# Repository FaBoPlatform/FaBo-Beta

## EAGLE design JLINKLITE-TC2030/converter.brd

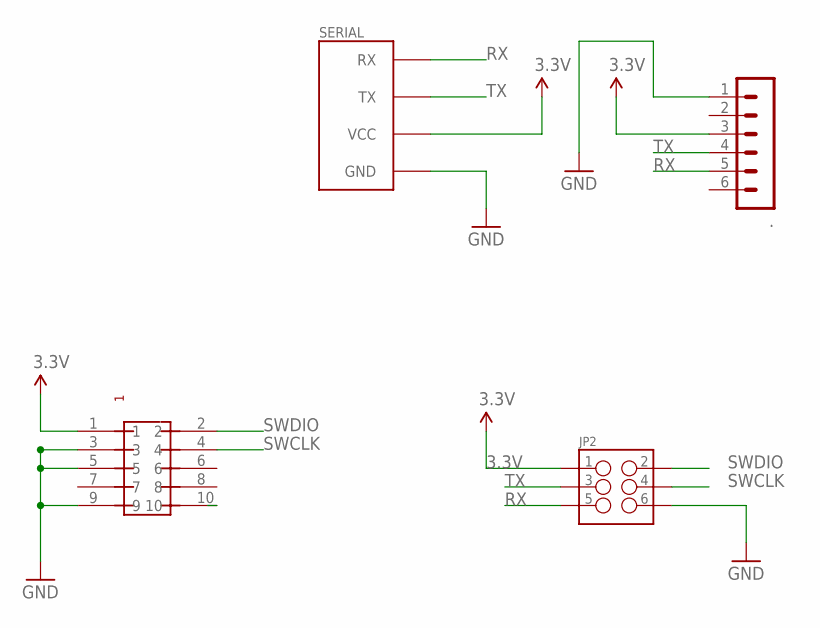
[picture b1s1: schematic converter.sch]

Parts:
.: MA06-1
JP2: M03X2; 2X3-SHROUDED
SERIAL: FABO_BRICK_SERIAL-CONNECTOR_I; FABO_BRICK_SERIAL_CONNECTOR_I
U$5: PIN-HEADER-SMT(1.27MM)2X5

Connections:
3.3V: ..3, JP2.1, SERIAL.VCC, U$5.1
GND: ..1, JP2.6, SERIAL.GND, U$5.3, U$5.5, U$5.9
RESET: U$5.10
RX: ..5, JP2.5, SERIAL.RX
SWCLK: JP2.4, U$5.4
SWDIO: JP2.2, U$5.2
TX: ..4, JP2.3, SERIAL.TX

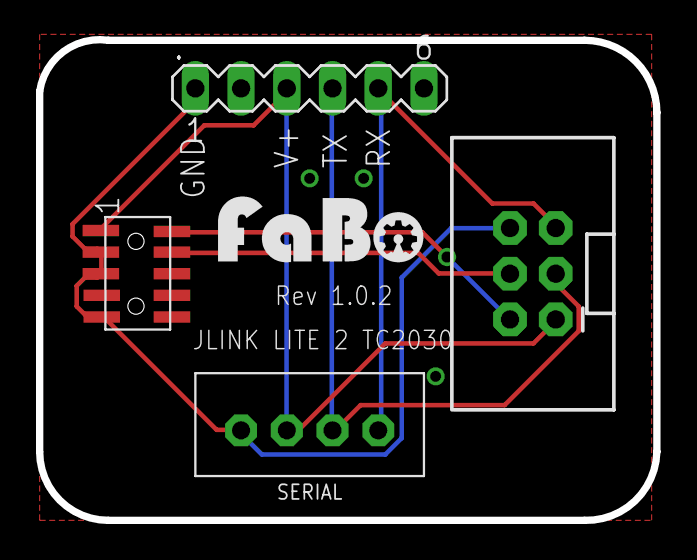
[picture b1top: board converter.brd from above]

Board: 2 copper layers, 34.3 x 26.7 mm, 5 parts (0 on the bottom side), 6 nets.

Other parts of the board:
U$1: LOGO_FABO_M

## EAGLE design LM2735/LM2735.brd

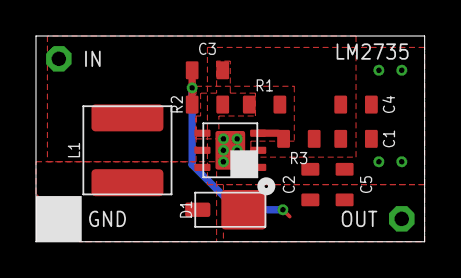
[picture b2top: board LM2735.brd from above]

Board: 2 copper layers, 21.6 x 11.4 mm, 15 parts (0 on the bottom side), 6 nets.

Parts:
C1, C2, C4, C5: 22uF X5R; 0603-NARROW
C3: 1000pF; 0603-NARROW
CN1, CN2, CN3: PIN_1X1_SMALL
D1: ST-MITE
IC1: WSON-6
L1: 22uH; NR5040
R1: 10k 1%; 0603-NARROW
R2: 30.1k 1%; 0603-NARROW
R3: 100k; 0603-NARROW
U$2: LOGO_FABO_MS_BOTTOM

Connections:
FB: C3.1, IC1.4, R1.2, R2.1
GND: C1.1, C2.1, C4.1, C5.1, CN2.1, IC1.1, IC1.5, IC1.7, R1.1
unnamed: IC1.3, R3.2
SW: D1.A, IC1.6, L1.2
VIN: C1.2, C4.2, CN1.1, IC1.2, L1.1, R3.1
VOUT: C2.2, C3.2, C5.2, CN3.1, D1.K, R2.2

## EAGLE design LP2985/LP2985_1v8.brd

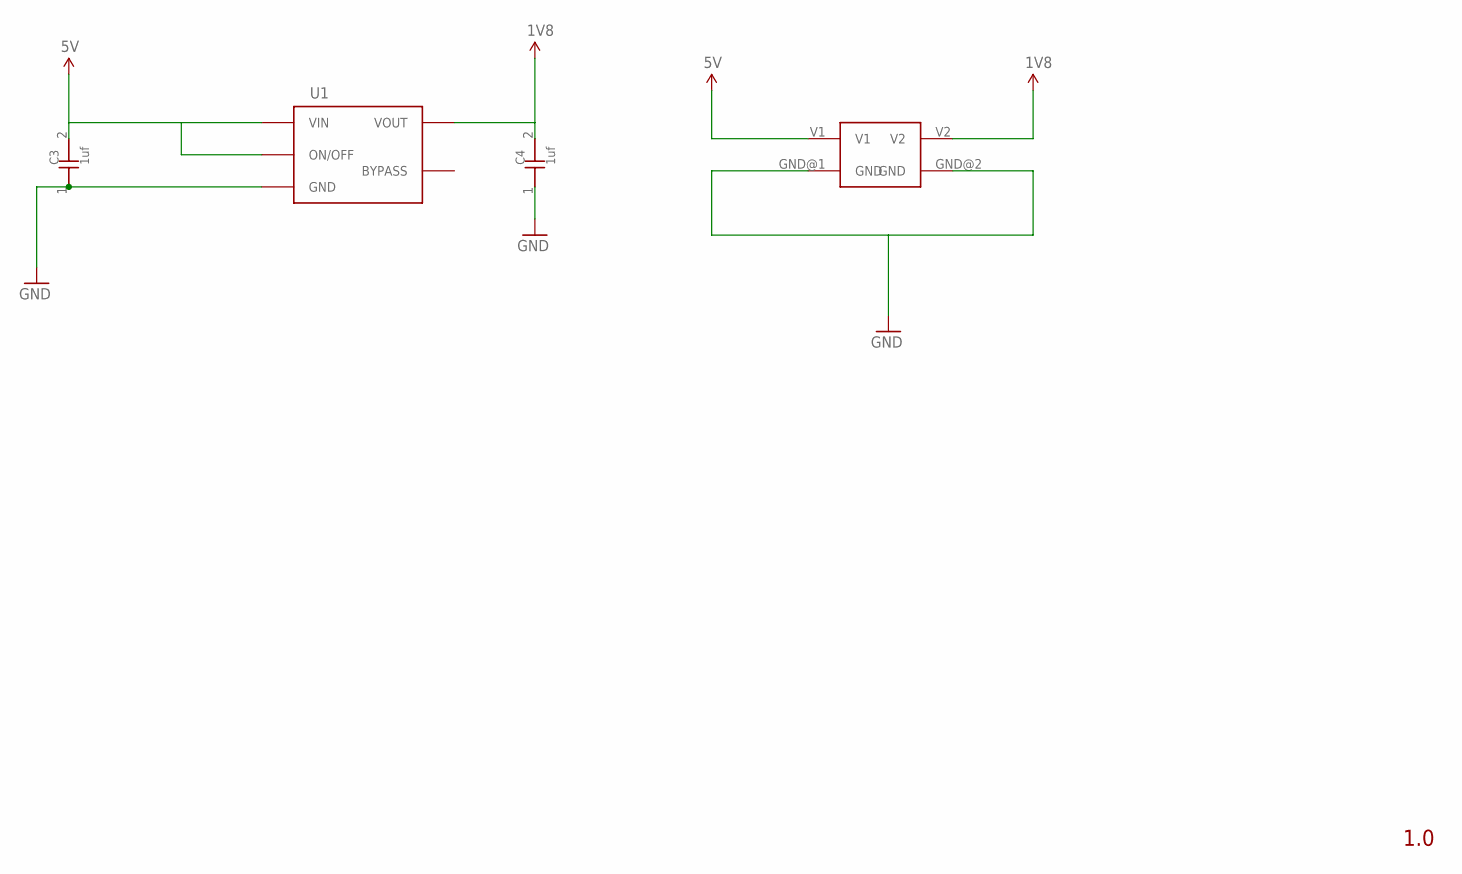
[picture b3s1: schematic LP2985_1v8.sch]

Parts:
C3, C4: 1uf; 0603
U1: LP2985-33DBVR; SOT_23_5
U$2: 4PIN-REGULATOR

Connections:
5V: C3.2, U1.1 (VIN), U1.3 (ON/OFF), U$2.V1
GND: C3.1, C4.1, U1.2 (GND), U$2.GND@1 (GND), U$2.GND@2 (GND)
VCC: C4.2, U1.5 (VOUT), U$2.V2

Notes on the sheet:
1.0

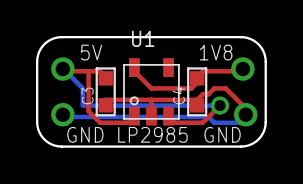
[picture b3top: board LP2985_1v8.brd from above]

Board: 2 copper layers, 12.7 x 6.1 mm, 4 parts (0 on the bottom side), 3 nets.

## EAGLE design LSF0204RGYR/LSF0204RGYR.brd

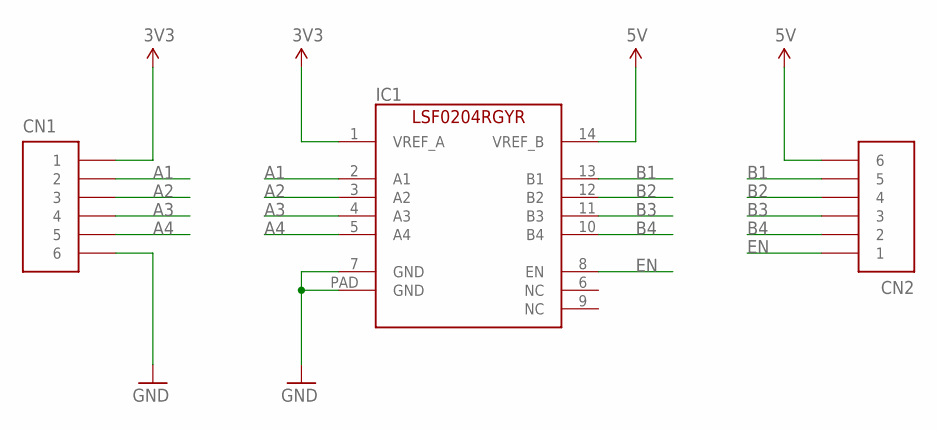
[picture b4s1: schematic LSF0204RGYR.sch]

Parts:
CN1, CN2: PIN_HEADER_1X6-SNEAKY; PIN_1X6_SNEAKY
IC1: LSF0204RGYR; VQFN-14

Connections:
3V3: CN1.1, IC1.1 (VREF_A)
5V: CN2.6, IC1.14 (VREF_B)
A1: CN1.2, IC1.2 (A1)
A2: CN1.3, IC1.3 (A2)
A3: CN1.4, IC1.4 (A3)
A4: CN1.5, IC1.5 (A4)
B1: CN2.5, IC1.13 (B1)
B2: CN2.4, IC1.12 (B2)
B3: CN2.3, IC1.11 (B3)
B4: CN2.2, IC1.10 (B4)
EN: CN2.1, IC1.8 (EN)
GND: CN1.6, IC1.7 (GND), IC1.PAD (GND)

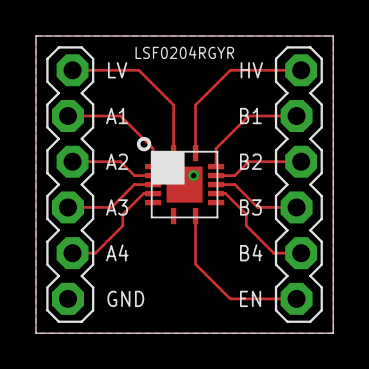
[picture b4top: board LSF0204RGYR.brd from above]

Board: 2 copper layers, 16.5 x 16.5 mm, 3 parts (0 on the bottom side), 12 nets.

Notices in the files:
parts and their libraries:
SparkFun-Connectors: Licensing: CC v3.0 Share-Alike You are welcome to use this library for commercial purposes.
FaBo-Template: Released under the Creative Commons Attribution-ShareAlike 4.0 License
https://creativecommons.org/licenses/by-sa/4.0
gclue: Released under the Creative Commons
